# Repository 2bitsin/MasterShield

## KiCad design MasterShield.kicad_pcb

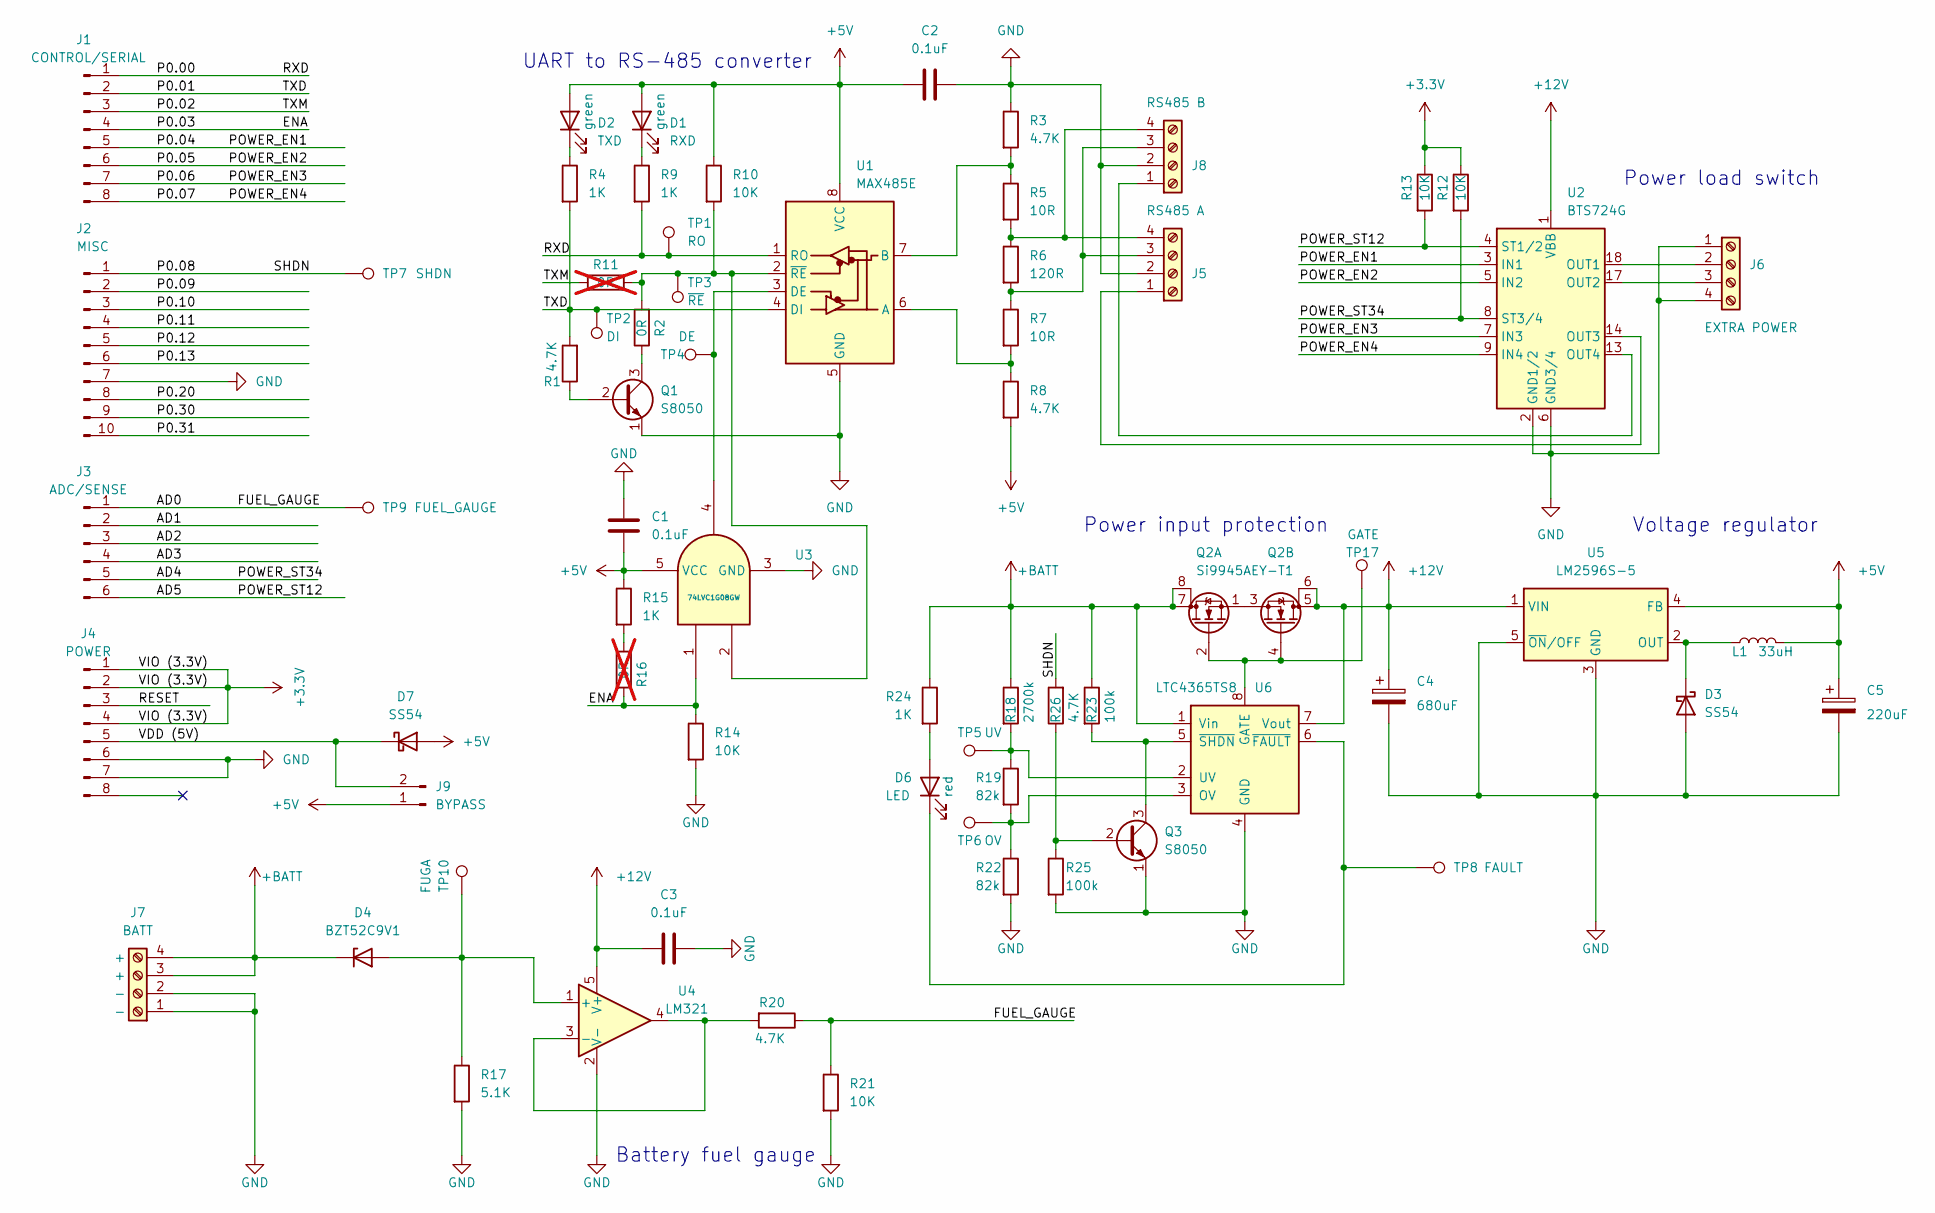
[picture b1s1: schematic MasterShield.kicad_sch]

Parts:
C1, C2, C3: 0.1uF; C_0805_2012Metric; LCSC C282732
C4: 680uF; CP_Elec_10x10.5; LCSC C7461236
C5: 220uF; CP_EIA-7343-15_Kemet-W_Pad2.25x2.55mm_HandSolder; LCSC C122304
D1: RXD; LED_0805_2012Metric; LCSC C84257
D2: TXD; LED_0805_2012Metric; LCSC C84257
D3, D7: SS54; D_SMA_Handsoldering; LCSC C22452
D4: BZT52C9V1; D_SOD-123; LCSC C5270765
D6: LED; LED_0805_2012Metric; LCSC C434431
J1: CONTROL/SERIAL; PinHeader_1x08_P2.54mm_Vertical
J2: MISC; PinHeader_1x10_P2.54mm_Vertical
J3: ADC/SENSE; PinHeader_1x06_P2.54mm_Vertical
J4: POWER; PinHeader_1x08_P2.54mm_Vertical
J5: RS485 A; TerminalBlock_4Ucon_1x04_P3.50mm_Horizontal
J6: EXTRA POWER; TerminalBlock_4Ucon_1x04_P3.50mm_Horizontal
J7: BATT; TerminalBlock_4Ucon_1x04_P3.50mm_Horizontal
J8: RS485 B; TerminalBlock_4Ucon_1x04_P3.50mm_Horizontal
J9: BYPASS; PinHeader_1x02_P2.54mm_Vertical
L1: 33uH; L_Abracon_ASPI-0630LR; LCSC C177245
Q1, Q3: S8050; SOT-23; LCSC C916390
Q2: Si9945AEY-T1; SOP-8_3.9x4.9mm_P1.27mm; LCSC C3040623
R1, R3, R8, R20, R26: 4.7K; R_0805_2012Metric; LCSC C17673
R2: 0R; R_0805_2012Metric; LCSC C17477
R4, R9, R15, R24: 1K; R_0805_2012Metric; LCSC C17513
R5, R7: 10R; R_0805_2012Metric; LCSC C7422239
R6: 120R; R_0805_2012Metric; LCSC C844392
R10, R12, R13, R14, R21: 10K; R_0805_2012Metric; LCSC C17414
R11, R16: 0R; R_0805_2012Metric; not fitted
R17: 5.1K; R_0805_2012Metric; LCSC C17673
R18: 2700k; R_0805_2012Metric; LCSC C2933540
R19, R22: 82k; R_0805_2012Metric; LCSC C17840
R23, R25: 100k; R_0805_2012Metric; LCSC C149504
TP1: RO; TestPoint_Pad_D2.0mm
TP2: DI; TestPoint_Pad_D2.0mm
TP3: ~{RE}; TestPoint_Pad_D2.0mm
TP4: DE; TestPoint_Pad_D2.0mm
TP5: UV; TestPoint_Pad_D2.0mm
TP6: OV; TestPoint_Pad_D2.0mm
TP7: SHDN; TestPoint_Pad_D2.0mm
TP8: FAULT; TestPoint_Pad_D2.0mm
TP9: FUEL_GAUGE; TestPoint_Pad_D2.0mm
TP10: FUGA; TestPoint_Pad_D2.0mm
TP17: GATE; TestPoint_Pad_D2.0mm
U1: MAX485E; SOIC-8_3.9x4.9mm_P1.27mm; LCSC C481667
U2: BTS724G; Infineon_PG-DSO-20-32; LCSC C82656
U3: 74LVC1G08GW; SOT-353_SC-70-5; LCSC C12512
U4: LM321; SOT-23-5; LCSC C18723612
U5: LM2596S-5; TO-263-5_TabPin3; LCSC C10002
U6: LTC4365TS8; TSOT-23-8; LCSC C514441

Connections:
+3.3V: J4.1, J4.2, J4.4, R12.1, R13.1
+5V: C1.1, C2.1, C5.1, D1.2 (A), D2.2 (A), D7.2 (A), J9.1, L1.2, R8.2, R10.1, R15.1, U1.8 (VCC), U3.5 (VCC), U5.4 (FB)
+12V: C3.1, C4.1, Q2.5 (D), Q2.6 (D), U2.1 (VBB), U2.10 (VBB), U2.11 (VBB), U2.12 (VBB), U2.15 (VBB), U2.16 (VBB), U2.19 (VBB), U2.20 (VBB), U4.5 (V+), U5.1 (VIN), U6.7 (Vout)
+BATT: D4.1 (K), J7.3, J7.4, Q2.7 (D), Q2.8 (D), R18.1, R23.1, R24.1, U6.1 (Vin)
/AD0: J3.1, R20.1, R21.1, TP9.1
/AD1: J3.2
/AD2: J3.3
/AD3: J3.4
/AD4: J3.5, R12.2, U2.8 (ST3/4)
/AD5: J3.6, R13.2, U2.4 (ST1/2)
/ENA: J1.4, R14.1, R16.1, U3.1
/P0.00: J1.1, R9.2, TP1.1, U1.1 (RO)
/P0.01: J1.2, R1.2, R4.2, TP2.1, U1.4 (DI)
/P0.02: J1.3, R11.1
/P0.04: J1.5, U2.3 (IN1)
/P0.05: J1.6, U2.5 (IN2)
/P0.06: J1.7, U2.7 (IN3)
/P0.07: J1.8, U2.9 (IN4)
/P0.08: J2.1, R26.2, TP7.1
/P0.09: J2.2
/P0.10: J2.3
/P0.11: J2.4
/P0.12: J2.5
/P0.13: J2.6
/P0.20: J2.8
/P0.30: J2.9
/P0.31: J2.10
/RESET: J4.3
/VDD (5V): D7.1 (K), J4.5, J9.2
GND: C1.2, C2.2, C3.2, C4.2, C5.2, D3.2 (A), J2.7, J4.6, J4.7, J5.2, J6.1, J6.4, J7.1, J7.2, J8.2, Q1.1 (E), Q3.1 (E), R3.1, R14.2, R17.2, R21.2, R22.2, R25.2, U1.5 (GND), U2.2 (GND1/2), U2.6 (GND3/4), U3.3 (GND), U4.2 (V-), U5.3 (GND), U5.5 (~ON/OFF), U6.4 (GND)
unnamed: D1.1 (K), R9.1
unnamed: D2.1 (K), R4.1
unnamed: D3.1 (K), L1.1, U5.2 (OUT)
unnamed: D4.2 (A), R17.1, TP10.1, U4.1 (+)
unnamed: D6.2 (A), R24.2
unnamed: D6.1 (K), TP8.1, U6.6 (~FAULT)
unnamed: J5.1, U2.14 (OUT3)
unnamed: J5.3, J8.3, R6.2, R7.1
unnamed: J5.4, J8.4, R5.2, R6.1
unnamed: J6.2, U2.18 (OUT1)
unnamed: J6.3, U2.17 (OUT2)
unnamed: J8.1, U2.13 (OUT4)
unnamed: Q1.2 (B), R1.1
unnamed: Q1.3 (C), R2.1
unnamed: Q2.2 (G), Q2.4 (G), TP17.1, U6.8 (GATE)
unnamed: Q2.1 (S), Q2.3 (S)
unnamed: Q3.2 (B), R25.1, R26.1
unnamed: Q3.3 (C), R23.2, U6.5 (~SHDN)
unnamed: R15.2, R16.2
unnamed: R7.2, R8.1, U1.6 (A)
unnamed: R3.2, R5.1, U1.7 (B)
unnamed: TP4.1, U1.3 (DE), U3.4
unnamed: R2.2, R10.2, R11.2, TP3.1, U1.2 (~RE), U3.2
unnamed: R20.2, U4.3 (-), U4.4
unnamed: R19.2, R22.1, TP6.1, U6.3 (OV)
unnamed: R18.2, R19.1, TP5.1, U6.2 (UV)

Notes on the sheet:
Battery fuel gauge
UART to RS-485 converter
Voltage regulator
Power input protection
Power load switch

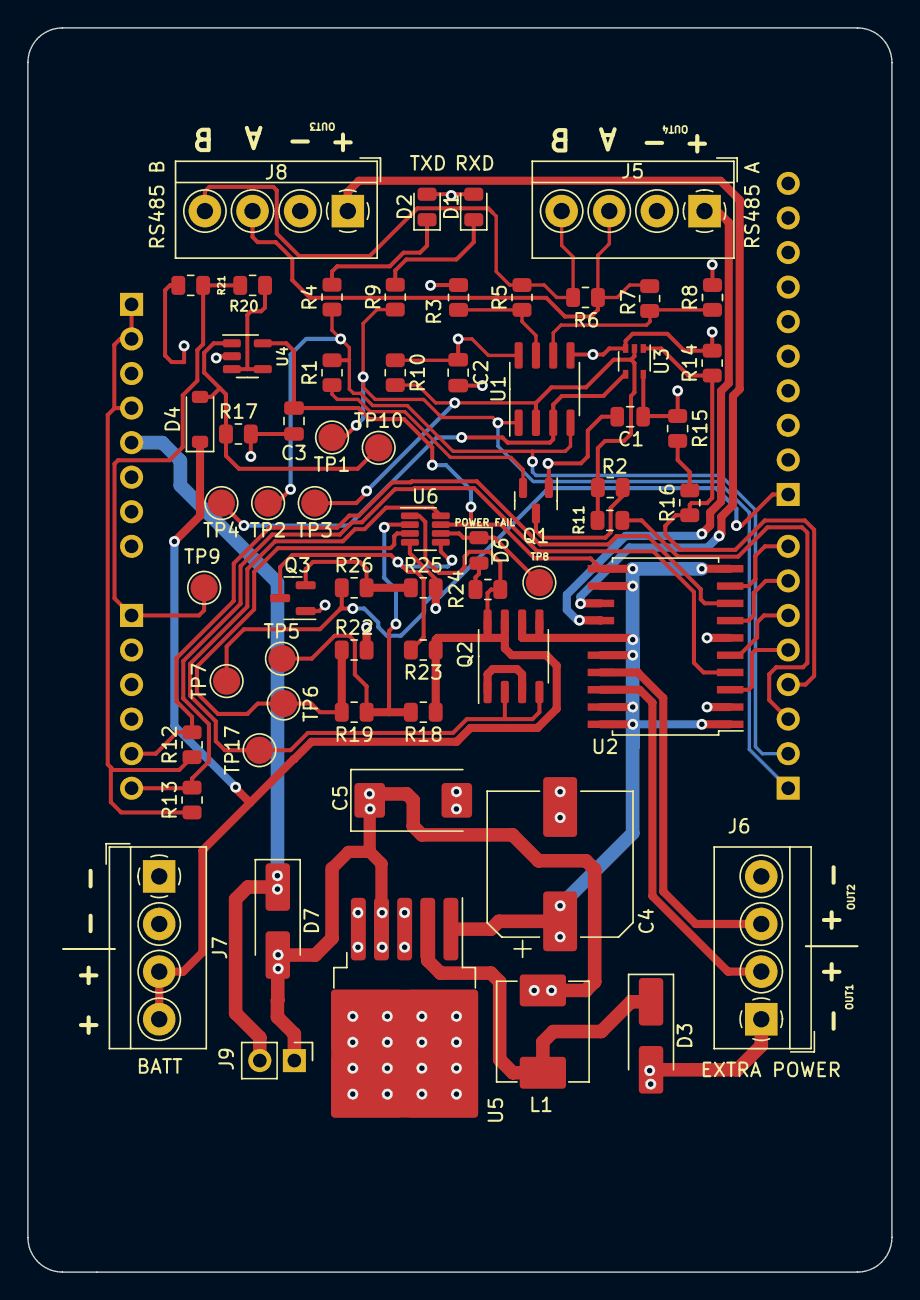
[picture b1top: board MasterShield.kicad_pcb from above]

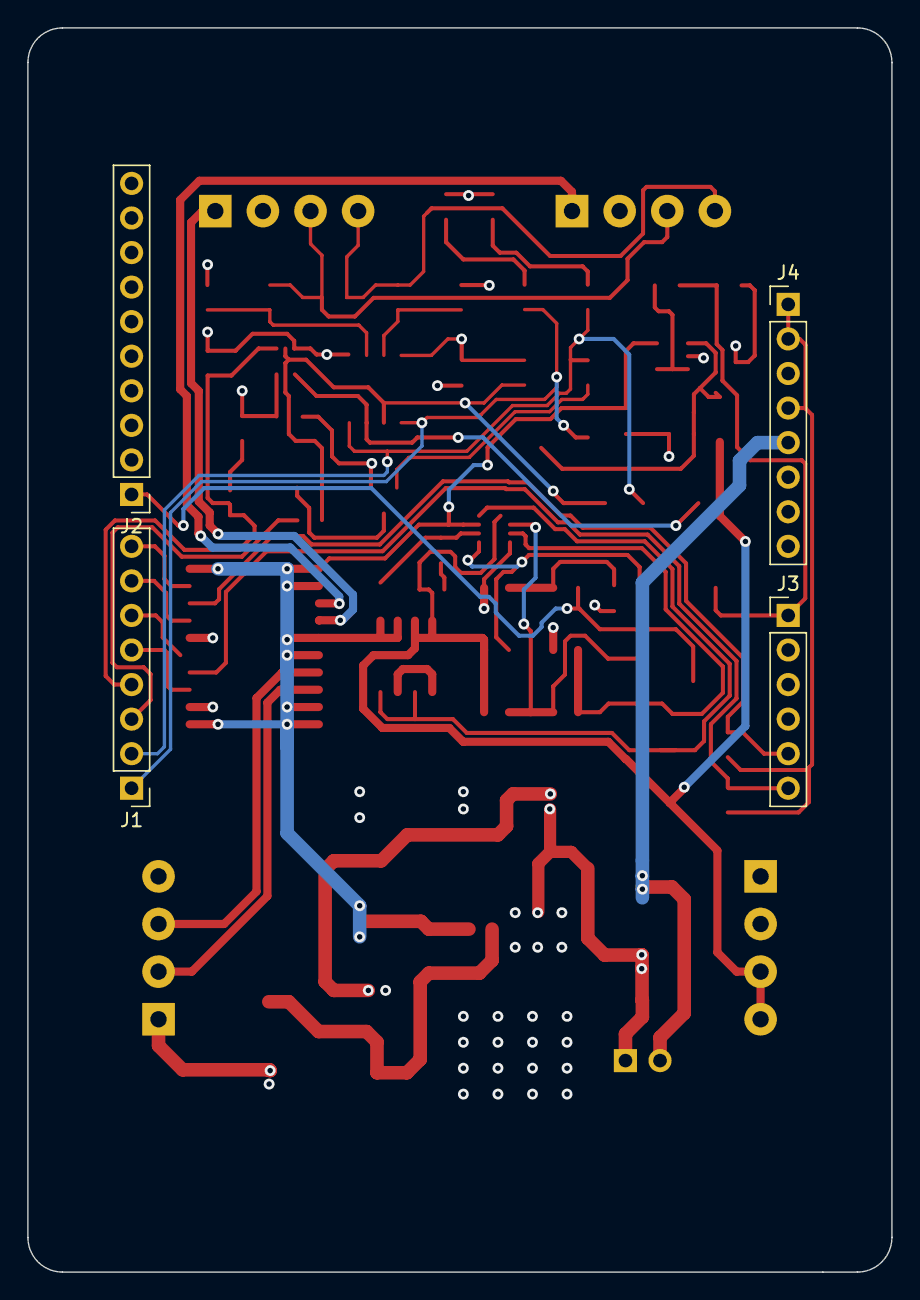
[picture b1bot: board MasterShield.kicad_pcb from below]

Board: 4 copper layers, 63.5 x 91.4 mm, 67 parts (4 on the bottom side), 44 nets.

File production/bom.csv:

Designator,Footprint,Quantity,Value,LCSC Part #
"C1, C2, C3",0805,3,0.1uF,C282732
C4,CP_Elec_10x10.5,1,680uF,C7461236
C5,CP_EIA-7343-15_Kemet-W_Pad2.25x2.55mm_HandSolder,1,220uF,C122304
D1,0805,1,RXD,C84257
D2,0805,1,TXD,C84257
"D3, D7",D_SMA_Handsoldering,2,SS54,C22452
D4,D_SOD-323_HandSoldering,1,10V,C85383
D5,D_SOD-323_HandSoldering,1,BZT52C3V3S,C5270765
D6,0805,1,LED,C434431
J1,PinHeader_1x08_P2.54mm_Vertical,1,CONTROL/SERIAL,
J2,PinHeader_1x10_P2.54mm_Vertical,1,MISC,
J3,PinHeader_1x06_P2.54mm_Vertical,1,ADC/SENSE,
J4,PinHeader_1x08_P2.54mm_Vertical,1,POWER,
J5,TerminalBlock_4Ucon_1x04_P3.50mm_Horizontal,1,RS485 A,
J6,TerminalBlock_4Ucon_1x04_P3.50mm_Horizontal,1,EXTRA POWER,
J7,TerminalBlock_4Ucon_1x04_P3.50mm_Horizontal,1,BATT,
J8,TerminalBlock_4Ucon_1x04_P3.50mm_Horizontal,1,RS485 B,
J9,PinHeader_1x02_P2.54mm_Vertical,1,BYPASS,
L1,L_Abracon_ASPI-0630LR,1,33uH,C177245
"Q1, Q3",SOT-23,2,S8050,C916390
Q2,SOP-8_3.9x4.9mm_P1.27mm,1,Si9945AEY-T1,C3040623
"R1, R17, R20, R26, R3, R8",0805,6,4.7K,C17673
"R10, R12, R13, R14, R21",0805,5,10K,C17414
"R15, R24, R4, R9",0805,4,1K,C17513
R18,0805,1,2700k,C2933540
"R19, R22",0805,2,82k,C17840
R2,0805,1,0R,C17477
"R23, R25",0805,2,100k,C149504
"R5, R7",0805,2,10R,C7422239
R6,0805,1,120R,C844392
TP1,TestPoint_Pad_D2.0mm,1,RO,
TP10,TestPoint_Pad_D2.0mm,1,FUGA,
TP17,TestPoint_Pad_D2.0mm,1,GATE,
TP2,TestPoint_Pad_D2.0mm,1,DI,
TP3,TestPoint_Pad_D2.0mm,1,~{RE},
TP4,TestPoint_Pad_D2.0mm,1,DE,
TP5,TestPoint_Pad_D2.0mm,1,UV,
TP6,TestPoint_Pad_D2.0mm,1,OV,
TP7,TestPoint_Pad_D2.0mm,1,SHDN,
TP8,TestPoint_Pad_D2.0mm,1,FAULT,
TP9,TestPoint_Pad_D2.0mm,1,FUEL_GAUGE,
U1,SOIC-8_3.9x4.9mm_P1.27mm,1,MAX485E,C481667
U2,Infineon_PG-DSO-20-32,1,BTS724G,C82656
U3,SOT-353_SC-70-5,1,74LVC1G08GW,C12512
U4,SOT-23-5,1,LM321,C18723612
U5,TO-263-5_TabPin3,1,LM2596S-5,C10002
U6,TSOT-23-8,1,LTC4365TS8,C514441

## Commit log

2024-01-25 Added OV/UV/RP protection
